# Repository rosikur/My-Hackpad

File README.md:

##Bongo Cat Keyboard.
A 3x3 keyboard with rotary Encoder and OLED display running bongo cat animation.
## Features
-3x3 key matrix
-Rotary Encoder with volume control 
-SSD1306 OLED display with animated bongo cat
## Setup
bash
qmk compile -kb bongo_keyboard -km default
qmk flash -kb bongo_keyboard -km default

## NOTICE
a lot has been ai generated by claude code  
Speacial Thanks to (at)nwii on Github! for the cat

##I didnt understand how to compile so good luck

##Bill of materials
1x Seeed XIAO RP2040
9x 1N4148 Diodes
9xMx Style switches
1x Ec11 Rotary Encoder
1x 0.91 Inch OLED disp
9x keycaps
4x M3x5x4mm heat inserts
4x M3x16mm screws

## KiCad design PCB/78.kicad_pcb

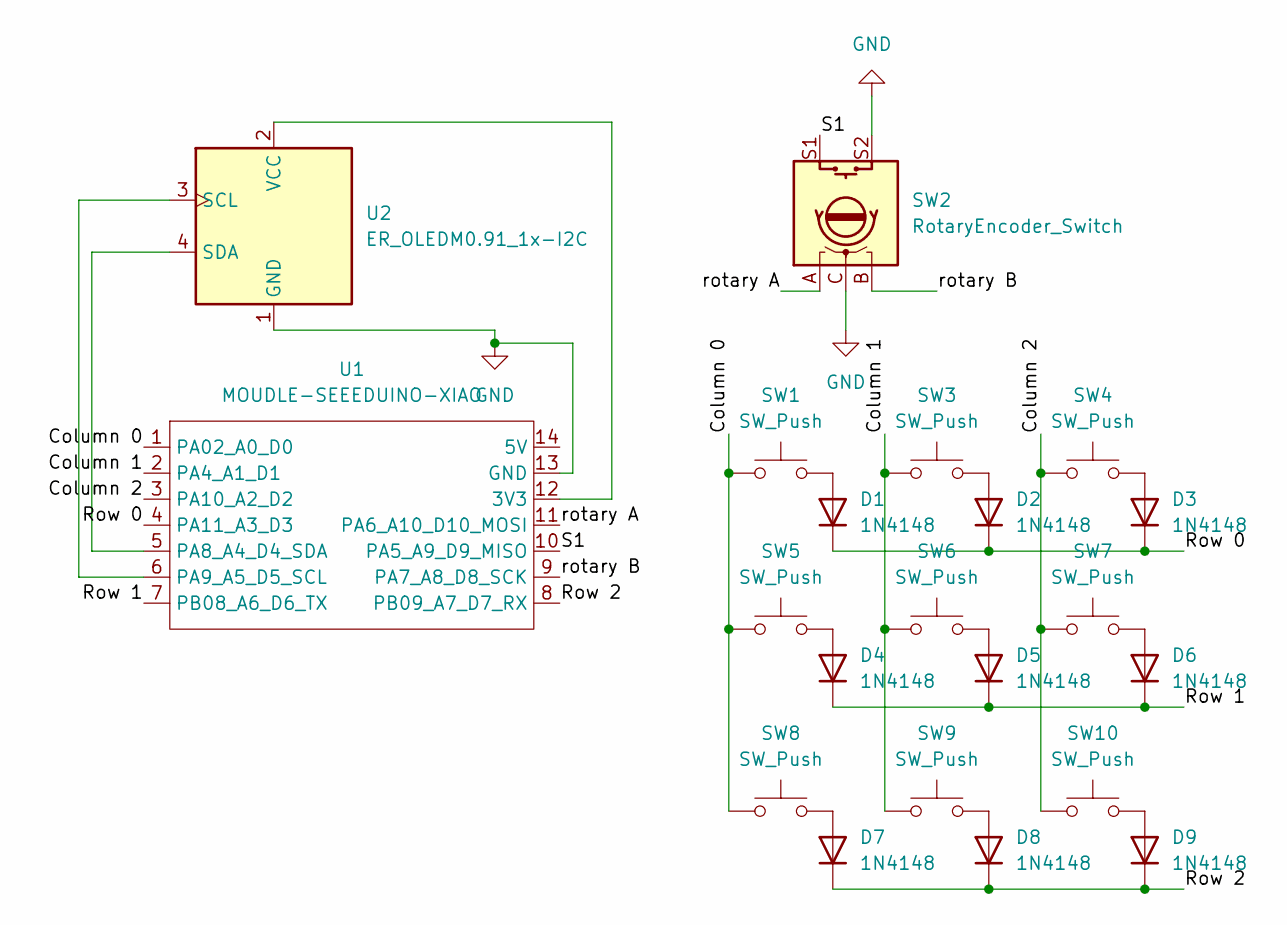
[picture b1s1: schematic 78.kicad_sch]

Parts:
D1, D2, D3, D4, D5, D6, D7, D8, D9: 1N4148; D_DO-35_SOD27_P7.62mm_Horizontal
SW1, SW3, SW4, SW5, SW6, SW7, SW8, SW9, SW10: SW_Push; SW_Cherry_MX_1.00u_PCB
SW2: RotaryEncoder_Switch; RotaryEncoder_Alps_EC11E-Switch_Vertical_H20mm
U1: MOUDLE-SEEEDUINO-XIAO; XIAO-Generic-Hybrid-14P-2.54-21X17.8MM
U2: ER_OLEDM0.91_1x-I2C

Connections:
/Column 0: SW1.1, SW5.1, SW8.1, U1.1 (PA02_A0_D0)
/Column 1: SW3.1, SW6.1, SW9.1, U1.2 (PA4_A1_D1)
/Column 2: SW4.1, SW7.1, SW10.1, U1.3 (PA10_A2_D2)
/Row 0: D1.1 (K), D2.1 (K), D3.1 (K), U1.4 (PA11_A3_D3)
/Row 1: D4.1 (K), D5.1 (K), D6.1 (K), U1.7 (PB08_A6_D6_TX)
/Row 2: D7.1 (K), D8.1 (K), D9.1 (K), U1.8 (PB09_A7_D7_RX)
/S1: SW2.S1, U1.10 (PA5_A9_D9_MISO)
/rotary A: SW2.A, U1.11 (PA6_A10_D10_MOSI)
/rotary B: SW2.B, U1.9 (PA7_A8_D8_SCK)
GND: SW2.C, SW2.S2, U1.13 (GND), U2.1 (GND)
unnamed: D1.2 (A), SW1.2
unnamed: D2.2 (A), SW3.2
unnamed: D3.2 (A), SW4.2
unnamed: D4.2 (A), SW5.2
unnamed: D5.2 (A), SW6.2
unnamed: D6.2 (A), SW7.2
unnamed: D7.2 (A), SW8.2
unnamed: D8.2 (A), SW9.2
unnamed: D9.2 (A), SW10.2
unnamed: U1.12 (3V3), U2.2 (VCC)
unnamed: U1.5 (PA8_A4_D4_SDA), U2.4 (SDA)
unnamed: U1.6 (PA9_A5_D5_SCL), U2.3 (SCL)

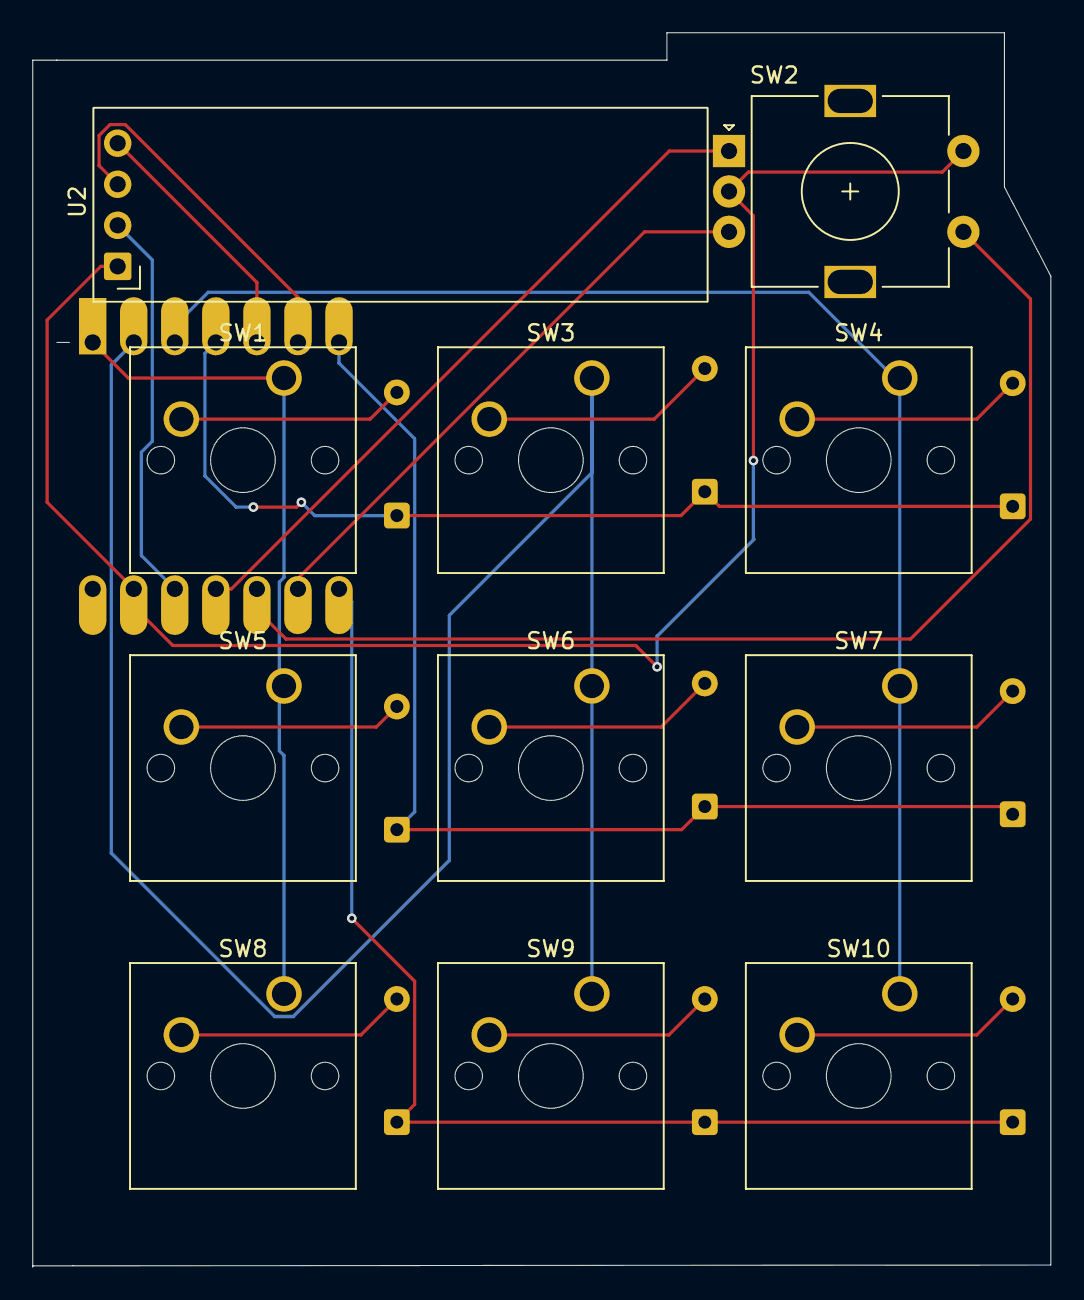
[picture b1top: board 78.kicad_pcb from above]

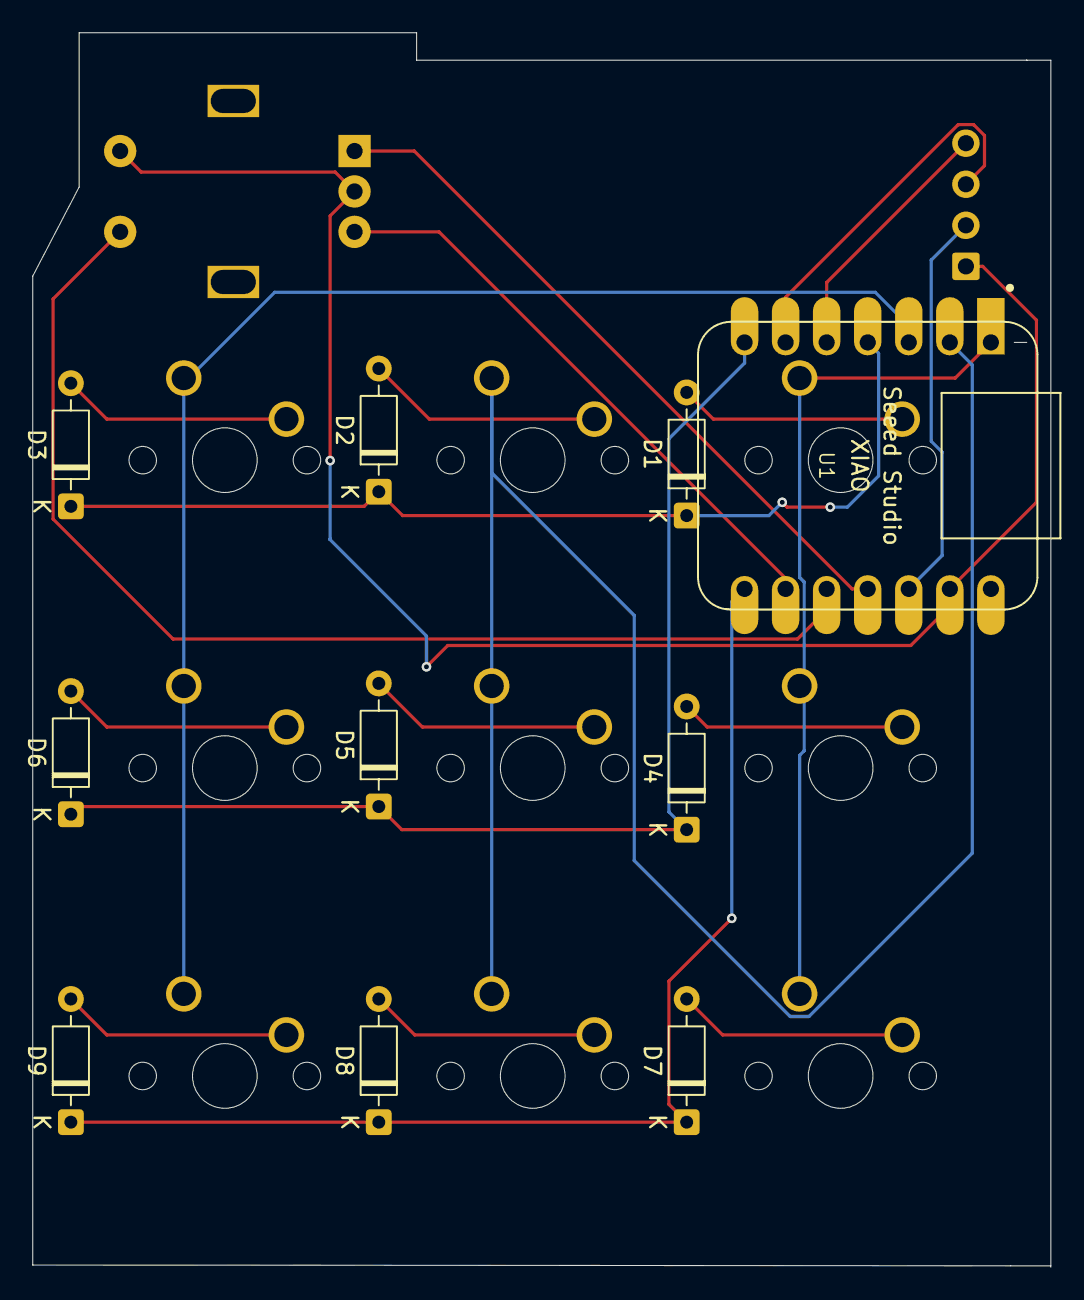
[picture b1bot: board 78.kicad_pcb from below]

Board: 2 copper layers, 63.0 x 76.4 mm, 21 parts (10 on the bottom side), 22 nets.

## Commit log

2026-06-14 Update README and clean up files
2026-06-14 Create CAD
2026-06-15 yyyyy
2026-06-15 Rename Fertig .3mf to Fertig .3mf
2026-06-15 Fix header format and add compilation note
    Corrected header formatting and added a note about compilation.
